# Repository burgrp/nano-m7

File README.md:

# Photon Mono M7 NanoDLP Modification

## Overview

Modification of the Anycubic Photon Mono M7 SLA printer to run NanoDLP. The original mainboard is replaced with a Raspberry Pi, a custom Nano-M7 controller board, and BHTM08 display driver. All mechanical parts and most electrical components are reused.

## Electronics

### Replaced
| Component | Replacement |
|-----------|-------------|
| Original mainboard | Raspberry Pi + Nano-M7 controller board + BHTM08 |

### Reused
- Display (DBM101M14K01) — driven by BHTM08 instead of original board
- UV lamp
- Z-axis stepper motor
- Limit switches
- Fans
- Power supply

## New Components

### Display Driver: BHTM08
- HDMI to MIPI DSI converter board by Shenzhen Aptus Technology
- Supports MONO LCD 9K/12K/14K
- Power: 5V via USB Type-C
- PCB size: 54x54mm, mounting holes φ3mm
- FPGA: Intel MAX 10 (10M13_9M16_V1.1)
- Interfaces: HDMI input, MIPI DSI output to display
- Spec: `doc/BHTM08 HDMI TO MIPI DSI DRIVER BOARD SPEC V1.0.pdf`

### CPU: Raspberry Pi
- Model TBD (Pi 4B or Pi 5 recommended for 14K image processing performance)
- Connected to Nano-M7 controller board via UART

### Nano-M7 Controller Board
- Custom board with connectors matching the original M7 control board for easy wiring
- PY32F030 MCU bridging the Raspberry Pi to printer peripherals
- See [Nano-M7 Controller Board](#nano-m7-controller-board-nano-m7kicad_sch) section for details

## Display: DBM101M14K01

- Manufacturer: Shenzhen Aptus Technology
- 10.1" TFT MONO (Transmissive), 13320x5120 pixels (14K)
- Outline: 230x142x1.06mm, Viewing area: 223.78x126.98mm
- Pixel size: 0.0168x0.0248mm
- Interface: 8-lane MIPI DSI, 51-pin FPC (connector: XVT:0-511822JT-5)
- Power: AVDD +5.5V, AVEE -5.5V, IOVCC 1.8V, IDD max 150mA
- Reset: active low, min 10µs pulse
- Spec: `doc/DBM101M14K01 Specification.pdf`

### NanoDLP Display Timing
| Parameter | Value |
|-----------|-------|
| Resolution | 13320x5120 |
| Frame rate | 15 Hz |
| PCLK | 359 MHz |
| HACT | 4440 |
| HS | 10 |
| HBP | 72 |
| HFP | 74 |
| H_total | 4596 |
| VACT | 5120 |
| VS | 4 |
| VBP | 16 |
| VFP | 77 |
| V_total | 5217 |

## Original Mainboard Connectors

Coordinates are XY in mm, origin at top-left corner of the board.

| Connector | Type | Pins | Position (mm) | Notes |
|-----------|------|------|---------------|-------|
| Projector LCD panel | FPC | 50 | 0, 25 | MIPI DSI to DBM101M14K01 |
| UI LCD panel | FPC | 50 | 0, 60 | Touchscreen UI display |
| Build platform sensor | JST 2mm | 4 | 20, 46 | I2C, unknown sensor (possibly strain/force for release detection) |
| NTC thermistor | JST 2.54mm | 2 | 70, 80 | NTC 100k on UV lamp heatsink |
| Z-axis stepper | JST 2.54mm | 4 | 90, 0 | Z-axis stepper motor |
| Lamp PWM | JST 2.54mm | 2 | 105, 0 | UV lamp PWM control |
| Lamp fan 0 | JST 2.54mm | 2 | 83, 35 | UV lamp cooling fan |
| Lamp fan 1 | JST 2.54mm | 2 | 93, 35 | UV lamp cooling fan |
| Lamp power supply | Latched, 3.75mm | 2 | 115, 25 | Power to UV lamp (connector type TBD) |
| Main power input | Terminal block | 2 | 115, 12 | Input from main PSU |
| External USB | JST 2mm | 5 | 116, 67 | External USB port |
| Front panel button | JST 2.54mm | 4 | 110, 50 | Power button + LED (TBC) |
| Low Z stop | JST 2.54mm | 3 | 85, 56 | Z-axis min endstop |
| PRO model interface | JST 2mm | 8 | 116, 50 | Interface for PRO variant (function TBD) |
| WiFi | IPX | 1 | 80, 60 | WiFi module connector |

## Nano-M7 Controller Board (nano-m7.kicad_sch)

Custom MCU board based on PY32F030K1xTx bridging the Raspberry Pi / NanoDLP controller to the printer's peripherals.

### MCU Pin Assignment

| GPIO | Net | Direction | Function |
|------|-----|-----------|----------|
| PF0 | Crystal | — | 16 MHz HSE in |
| PF1 | Crystal | — | 16 MHz HSE out |
| PF2 | NRST | — | Reset |
| PA0 | LAMP_NTC_MCU | IN | NTC thermistor ADC |
| PA2 | I2C_SDA | I/O | Build platform sensor |
| PA3 | I2C_SCL | I/O | Build platform sensor |
| PA4 | Z_STOP_LOW | IN | Z-axis min endstop |
| PA5 | FP_BTN | IN | Front panel button |
| PA6 | LAMP_PWM | OUT | UV lamp PWM |
| PA7 | LAMP_FAN_MCU | OUT | Lamp fan P-MOS gate |
| PA8 | ZS_STEP | OUT | Z stepper STEP |
| PA9 | PY_RXD | IN | UART RX from Raspberry Pi |
| PA10 | PY_TXD | OUT | UART TX to Raspberry Pi |
| PB1 | LED | OUT | Status LED |
| PB3 | LAMP_POWER_MCU | OUT | UV lamp power P-MOS gate |
| PB4 | ZS_DIR | OUT | Z stepper DIR |
| PB5 | FP_LED | OUT | Front panel LED |

### Command Interface

Communication between NanoDLP (Raspberry Pi) and MCU is via UART at 115200 baud (PA9/PA10).

Custom non-standard command set (not GCODE-compatible).

| Command | Parameters | Description |
|---------|------------|-------------|
| `ZH` | — | Home Z axis to min endstop |
| `ZM` | `S<steps> F<Hz>` | Move Z relative by steps at step frequency F (Hz). Positive = up, negative = down. |
| `GET` | — | Report Z position (Z:n steps), endstop (ES:0/1), button (BTN:0/1), temperature (NTC:n°C) |
| `LFE` | — | Lamp fan enable (P-MOS) |
| `LFD` | — | Lamp fan disable (P-MOS) |
| `LPE` | — | UV lamp power enable (P-MOS) |
| `LPD` | — | UV lamp power disable (P-MOS) |
| `LPI` | `I<0-255>` | Set UV lamp PWM intensity |
| `FPLE` | — | Front panel LED on |
| `FPLD` | — | Front panel LED off |
| `SCHI` | `I<ms>` | Set system check interval in ms |

### Controller Board to Raspberry Pi 4 wiring

Wired by ribbon cable:

## Verified

- BHTM08 works correctly with DBM101M14K01
- Tested by connecting a notebook via HDMI to BHTM08, which drove the display successfully

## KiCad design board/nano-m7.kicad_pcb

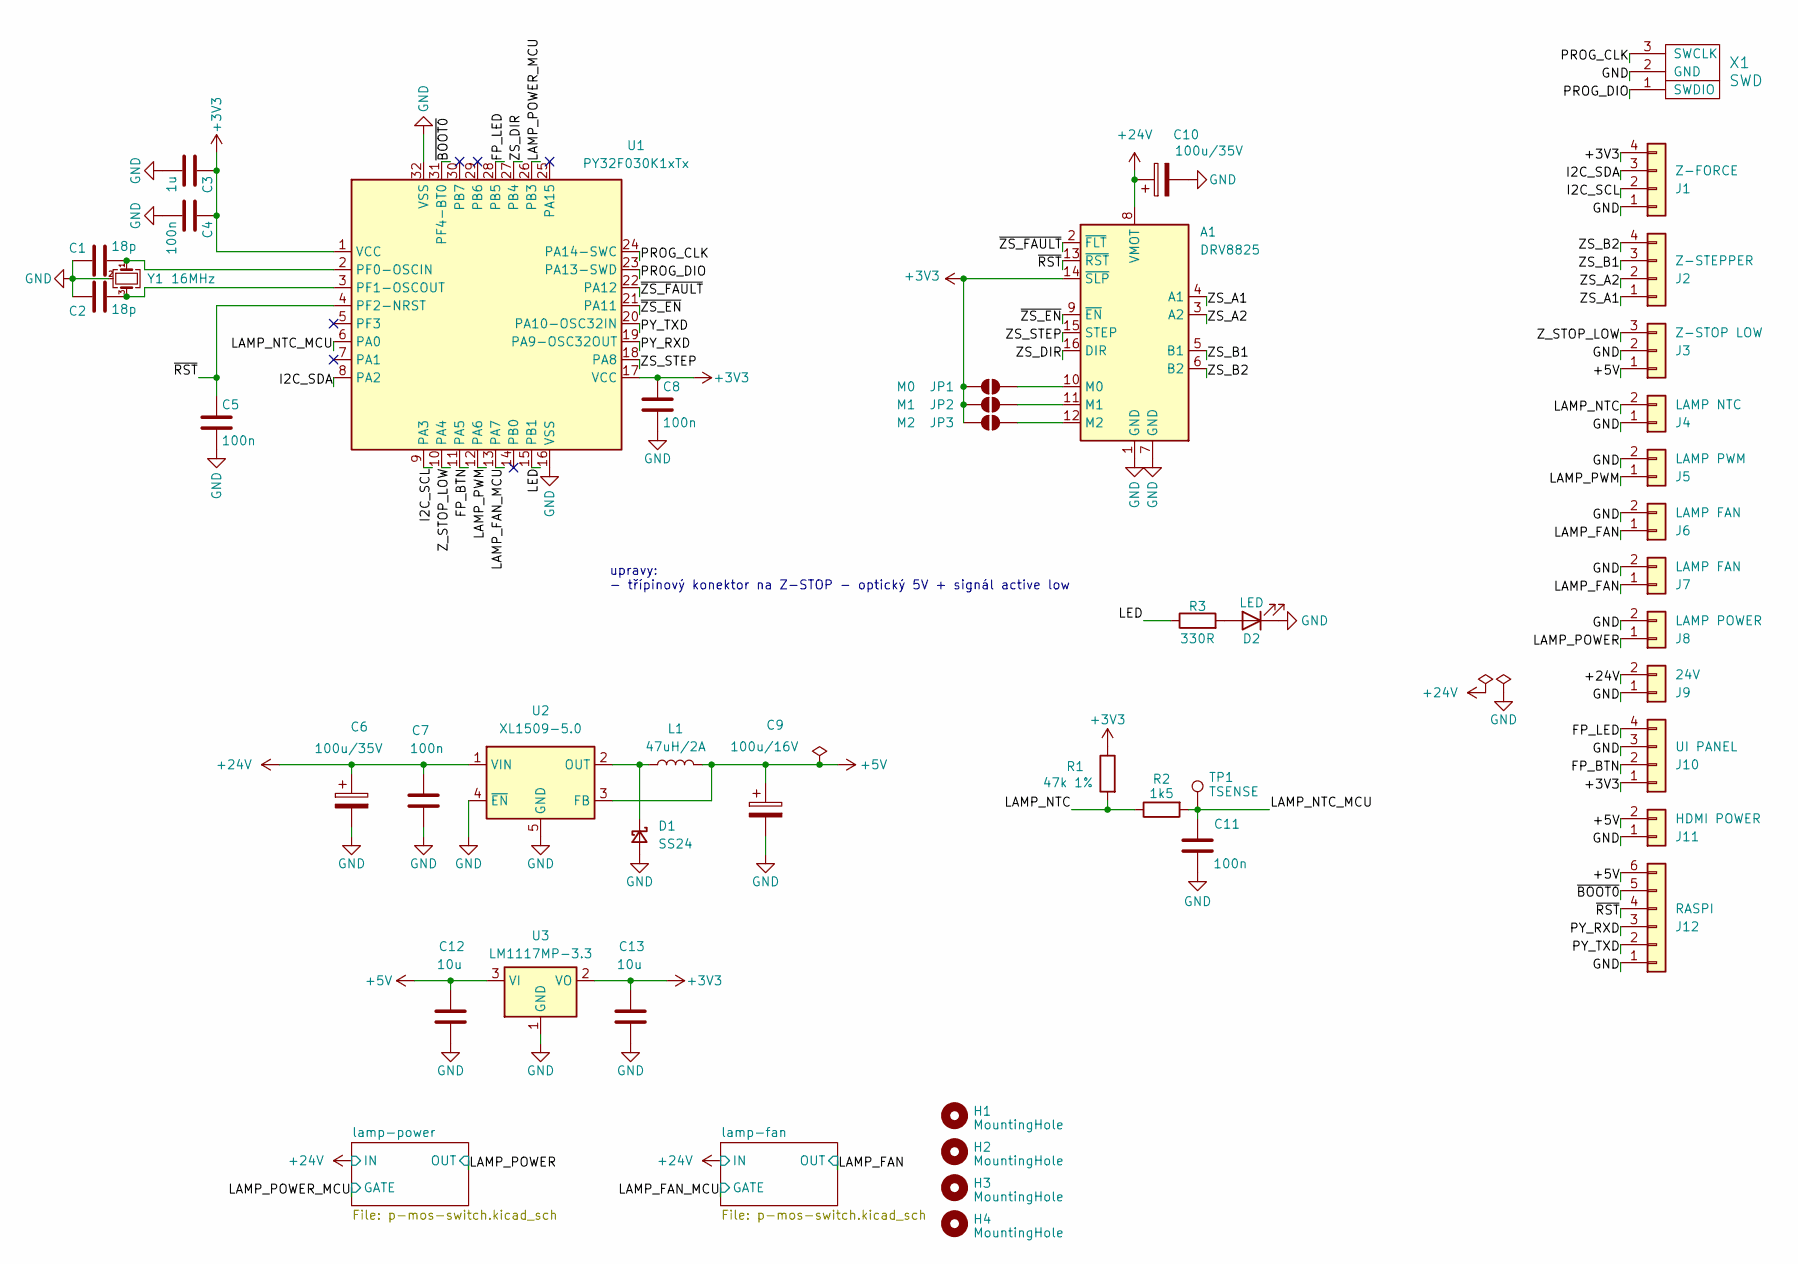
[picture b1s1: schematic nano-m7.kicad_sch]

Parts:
A1: DRV8825; Pololu_Breakout-16_15.2x20.3mm
C1, C2: 18p; C_0805_2012Metric
C3: 1u; C_0805_2012Metric
C4, C5, C7, C8, C11: 100n; C_0805_2012Metric
C6: 100u/35V; CP_Elec_6.3x5.8
C9: 100u/16V; CP_Elec_6.3x5.8
C10: 100u/35V; CP_Elec_6.3x5.8; LCSC C178540
C12, C13: 10u; C_0805_2012Metric
D1: SS24; D_SMA_Handsoldering
D2: LED; LED_0805_2012Metric
H1, H2, H3, H4: MountingHole; MountingHole_3.7mm_Pad_Via
J1: Z-FORCE; JST_PH_B4B-PH-K_1x04_P2.00mm_Vertical
J2: Z-STEPPER; JST_XH_B4B-XH-A_1x04_P2.50mm_Vertical
J3: Z-STOP LOW; JST_XH_B3B-XH-A_1x03_P2.50mm_Vertical
J4: LAMP NTC; JST_XH_B2B-XH-A_1x02_P2.50mm_Vertical
J5: LAMP PWM; JST_XH_B2B-XH-A_1x02_P2.50mm_Vertical
J6, J7: LAMP FAN; JST_XH_B2B-XH-A_1x02_P2.50mm_Vertical
J8: LAMP POWER; JST_VH_B2P-VH-B_1x02_P3.96mm_Vertical
J9: 24V; DG142R-2-5.08
J10: UI PANEL; JST_XH_B4B-XH-A_1x04_P2.50mm_Vertical
J11: HDMI POWER; JST_XH_B2B-XH-A_1x02_P2.50mm_Vertical
J12: RASPI; PinHeader_1x06_P2.54mm_Vertical
JP1: M0; SolderJumper-2_P1.3mm_Open_TrianglePad1.0x1.5mm
JP2: M1; SolderJumper-2_P1.3mm_Open_TrianglePad1.0x1.5mm
JP3: M2; SolderJumper-2_P1.3mm_Open_TrianglePad1.0x1.5mm
L1: 47uH/2A; L_Sunlord_MWSA0604S; LCSC C49190176
R1: 47k 1%; R_0805_2012Metric
R2: 1k5; R_0805_2012Metric
R3: 330R; R_0805_2012Metric
TP1: TSENSE; TestPoint_THTPad_D2.0mm_Drill1.0mm
U1: PY32F030K1xTx; LQFP-32_7x7mm_P0.8mm
U2: XL1509-5.0; SOIC-8_3.9x4.9mm_P1.27mm
U3: LM1117MP-3.3; SOT-223-3_TabPin2
X1: SWD
Y1: 16MHz; Crystal_SMD_3225-4Pin_3.2x2.5mm

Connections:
+3V3: A1.14 (~SLP), C3.1, C4.1, C8.1, C13.1, J1.4, J10.1, JP1.1 (A), JP2.1 (A), JP3.1 (A), R1.1, U1.1 (VCC), U1.17 (VCC), U3.2 (VO)
+5V: C9.1, C12.1, J3.1, J11.2, J12.6, L1.2, U2.3 (FB), U3.3 (VI)
+24V: A1.8 (VMOT), C6.1, C7.1, C10.1, J9.2, U2.1 (VIN); also elsewhere on the board
/FP_BTN: J10.2, U1.11 (PA5)
/FP_LED: J10.4, U1.28 (PB5)
/I2C_SCL: J1.2, U1.9 (PA3)
/I2C_SDA: J1.3, U1.8 (PA2)
/LAMP_FAN: J6.1, J7.1; also elsewhere on the board
/LAMP_FAN_MCU: U1.13 (PA7); also elsewhere on the board
/LAMP_NTC: J4.2, R1.2, R2.1
/LAMP_NTC_MCU: C11.2, R2.2, TP1.1, U1.6 (PA0)
/LAMP_POWER: J8.1; also elsewhere on the board
/LAMP_POWER_MCU: U1.26 (PB3); also elsewhere on the board
/LAMP_PWM: J5.1, U1.12 (PA6)
/LED: R3.1, U1.15 (PB1)
/PROG_CLK: U1.24 (PA14-SWC), X1.3 (SWCLK)
/PROG_DIO: U1.23 (PA13-SWD), X1.1 (SWDIO)
/PY_RXD: J12.3, U1.19 (PA9-OSC32OUT)
/PY_TXD: J12.2, U1.20 (PA10-OSC32IN)
/ZS_A1: A1.4 (A1), J2.1
/ZS_A2: A1.3 (A2), J2.2
/ZS_B1: A1.5 (B1), J2.3
/ZS_B2: A1.6 (B2), J2.4
/ZS_DIR: A1.16 (DIR), U1.27 (PB4)
/ZS_STEP: A1.15 (STEP), U1.18 (PA8)
/Z_STOP_LOW: J3.3, U1.10 (PA4)
/~BOOT0: J12.5, U1.31 (PF4-BT0)
/~RST: A1.13 (~RST), C5.1, J12.4, U1.4 (PF2-NRST)
/~ZS_EN: A1.9 (~EN), U1.21 (PA11)
/~ZS_FAULT: A1.2 (~FLT), U1.22 (PA12)
GND: A1.1 (GND), A1.7 (GND), C1.1, C2.1, C3.2, C4.2, C5.2, C6.2, C7.2, C8.2, C9.2, C10.2, C11.1, C12.2, C13.2, D1.2 (A), D2.1 (K), J1.1, J3.2, J4.1, J5.2, J6.2, J7.2, J8.2, J9.1, J10.3, J11.1, J12.1, U1.16 (VSS), U1.32 (VSS), U2.4 (~EN), U2.5 (GND), U2.6 (GND), U2.7 (GND), U2.8 (GND), U3.1 (GND), X1.2 (GND), Y1.2 (G), Y1.4 (G); also elsewhere on the board
unnamed: A1.10 (M0), JP1.2 (B)
unnamed: A1.11 (M1), JP2.2 (B)
unnamed: A1.12 (M2), JP3.2 (B)
unnamed: D1.1 (K), L1.1, U2.2 (OUT)
unnamed: D2.2 (A), R3.2
unnamed: C1.2, U1.2 (PF0-OSCIN), Y1.1
unnamed: C2.2, U1.3 (PF1-OSCOUT), Y1.3

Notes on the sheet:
upravy: - třípinový konektor na Z-STOP - optický 5V + signál active low

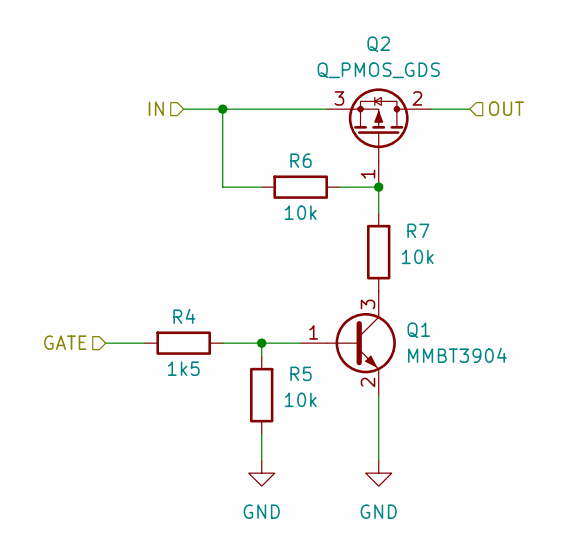
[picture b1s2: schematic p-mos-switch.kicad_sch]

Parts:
Q1: MMBT3904; SOT-23
Q2: Q_PMOS_GDS; TO-252-2
R4: 1k5; R_0805_2012Metric
R5, R6, R7: 10k; R_0805_2012Metric

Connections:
+24V: Q2.3 (S), R6.2; also elsewhere on the board
/LAMP_POWER: Q2.2 (D); also elsewhere on the board
/LAMP_POWER_MCU: R4.2; also elsewhere on the board
GND: Q1.2 (E), R5.1; also elsewhere on the board
unnamed: Q1.1 (B), R4.1, R5.2
unnamed: Q1.3 (C), R7.1
unnamed: Q2.1 (G), R6.1, R7.2

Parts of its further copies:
Q3: MMBT3904; SOT-23
Q4: Q_PMOS_GDS; TO-252-2
R8: 1k5; R_0805_2012Metric
R9, R10, R11: 10k; R_0805_2012Metric

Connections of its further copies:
+24V: Q4.3 (S), R10.2; also elsewhere on the board
/LAMP_FAN: Q4.2 (D); also elsewhere on the board
/LAMP_FAN_MCU: R8.2; also elsewhere on the board
GND: Q3.2 (E), R9.1; also elsewhere on the board
unnamed: Q3.1 (B), R8.1, R9.2
unnamed: Q3.3 (C), R11.1
unnamed: Q4.1 (G), R10.1, R11.2

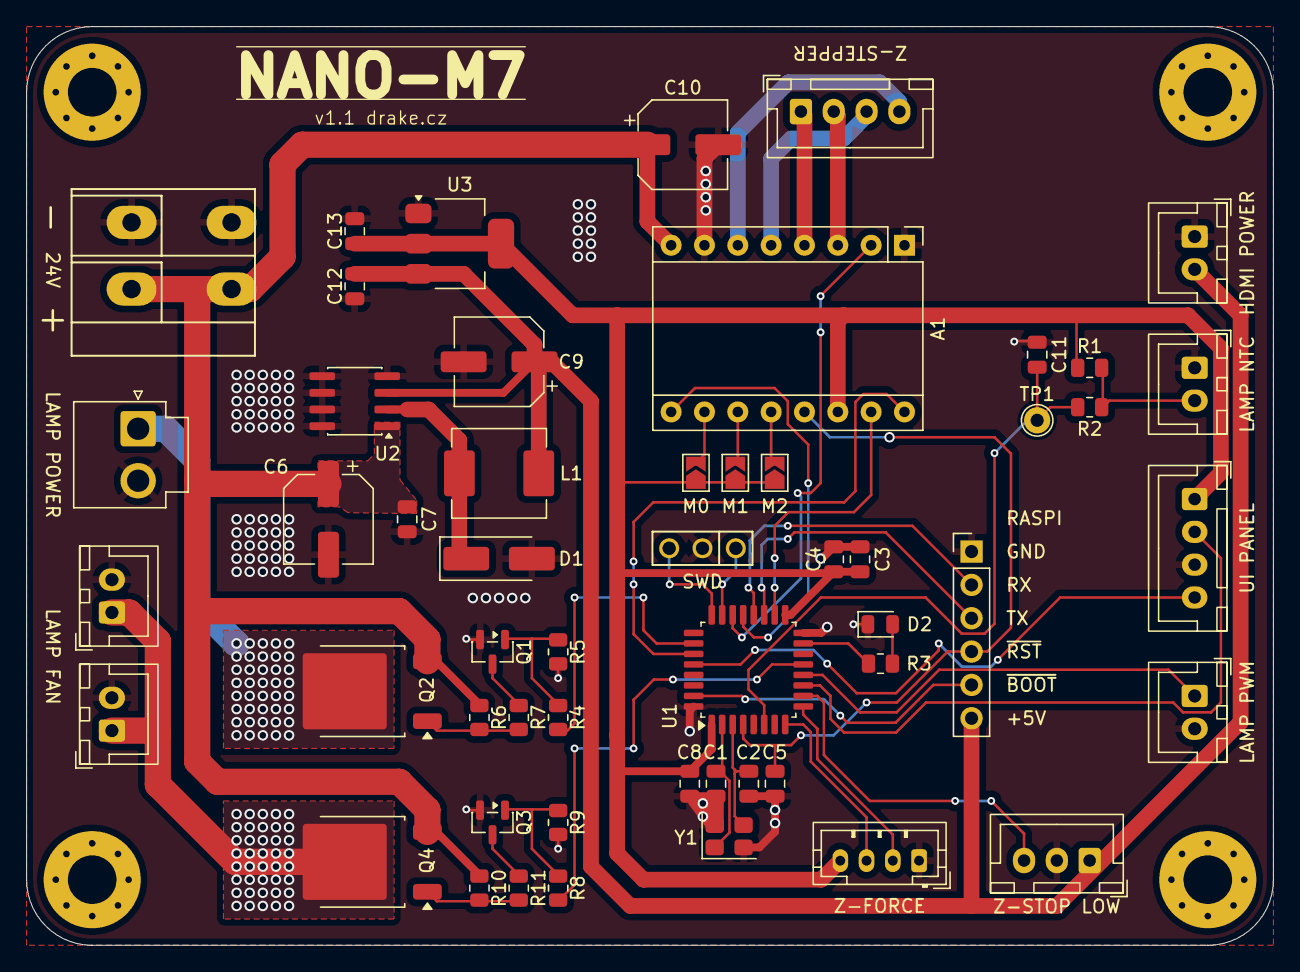
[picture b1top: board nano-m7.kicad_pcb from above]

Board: 2 copper layers, 95.0 x 70.0 mm, 57 parts (0 on the bottom side), 44 nets.

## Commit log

2026-03-05 Add design documentation for Photon Mono M7 NanoDLP modification
2026-03-05 Add various documentation files and teardown images for reference
2026-03-05 Refactor code structure for improved readability and maintainability
2026-03-05 embed image
2026-03-13 board v1.0
2026-03-31 Update documentation and code structure
    - Corrected the path for TinyGo source code in CLAUDE.md
    - Updated plot directory in nano-m7.kicad_pro
    - Removed lock file ~nano-m7.kicad_sch.lck
    - Enhanced Makefile with garbage collection options
    - Updated main.go to set clock frequency and configure UART pins
    - Modified size-report.html for accurate size representation
2026-04-05 Refactor build settings and improve health check functionality
2026-04-05 Refactor Makefile and update handler function signature to include commands parameter
2026-04-05 Implement GCode command handling and add unit tests for command parsing
2026-04-05 Update GCode command handling to include M900 for health check interval adjustment
2026-04-05 Add pin configuration for lamp fan and implement M801 GCode command for fan control
2026-04-05 Add lamp PWM control and update main function for new pin configuration
2026-04-05 Refactor lamp initialization and add syscheck functionality for memory monitoring
2026-04-05 Update lamp initialization to include timer parameter and enable TIM3 peripheral clock in main function
2026-04-05 Remove redundant LED pin configuration from main function and ensure it's set in syscheck initialization
2026-04-05 Add front panel functionality with LED control and update main logic
2026-04-05 Implement front panel and Z-axis functionality with reporting capabilities
2026-04-05 Remove note on lamp power activation from README
2026-04-05 Update README to clarify controller board naming and connection details
2026-04-05 Add notes on new 5V source and LDO requirements to schematic
2026-04-06 Update lamp and z-axis functionality with NTC thermistor integration and ADC setup
2026-04-06 Enhance Z-axis functionality with stepper motor control and ISR integration; update front panel button configuration
2026-05-04 Refactor UART pin configuration for clarity and consistency
2026-05-04 Add _autosave* to .gitignore to prevent autosave files from being tracked
2026-05-04 Add ZAxis enable pin and update related functionality
2026-05-04 Add auto_saved pattern to .gitignore to prevent tracking of auto-saved files
2026-05-04 Update command interface and improve validation logic for custom commands
2026-05-04 Re-enable memory statistics logging in SysCheck goroutine
2026-05-04 Update schematic text for next version 1.2 with hardware pull-up for ZS_EN
2026-05-04 Add initial implementation of NanoM7 host application
    - Create JSON profile for default print settings.
    - Implement display management using SDL2 for rendering images.
    - Set up Go module and dependencies for the project.
    - Develop main application logic to initialize store, serial communication, and display.
    - Implement printer control logic with state management and job handling.
    - Add serial communication client for sending commands and receiving status.
2026-05-05 Refactor printer setup and slicing logic; add STL parsing and ZIP output functionality
2026-05-05 Add HDMI output support and profiling options; refactor STL parsing logic
2026-05-05 Remove unused components and default profile
    - Deleted the default print profile (1.json) from the profiles directory.
    - Removed the display package and its associated functionality from the host.
    - Eliminated the main application logic in main.go, including server setup and initialization.
    - Removed the printer package, which handled printing logic and state management.
    - Deleted the serial communication client used for printer communication.
    - Removed the store package responsible for managing profiles and plates.
2026-05-05 Add 3DBenchy STL file for benchmarking
2026-05-05 Add initial firmware and hardware support for Nano-M7
    - Create symbol library table for KiCad with Drake and MCU_Puya_PY32F.
    - Add .gitignore file to peri-fw to exclude build artifacts.
    - Implement Makefile for building, flashing, and testing the firmware.
    - Add GCode command handler in handler.go for processing GCode commands.
    - Implement unit tests for GCode command handler in handler_test.go.
    - Initialize Go module for firmware in go.mod.
2026-05-05 SAC base compiles
2026-05-05 Refactor web UI: Remove unused assets and styles, update configuration
    - Deleted unused favicon images (PNG and SVG).
    - Removed group header SVG and home page CSS/JS files.
    - Cleaned up settings page CSS/JS files.
    - Removed virtual page CSS/JS files.
    - Updated system configuration structure, removing obsolete fields.
    - Refactored user controller to use new logging method.
2026-05-05 sbc-app base
2026-05-14 feat: Upgrade Font Awesome to version 7.2.0 and update styles
    - Updated Font Awesome CSS files to version 7.2.0, including changes to font-family and deprecated properties.
    - Added new font files for Nunito Sans (Black, Bold, Regular) to enhance UI typography.
    - Enhanced common CSS with new styles for navigation and printer name display.
    - Refactored common.js to improve the decoration function and update printer name dynamically.
    - Modified home.page.js to reflect updated title and structure.
    - Cleaned up ui_api.go by removing unused status management code.
2026-05-26 fix: Update active link styling and correct navigation link labels
